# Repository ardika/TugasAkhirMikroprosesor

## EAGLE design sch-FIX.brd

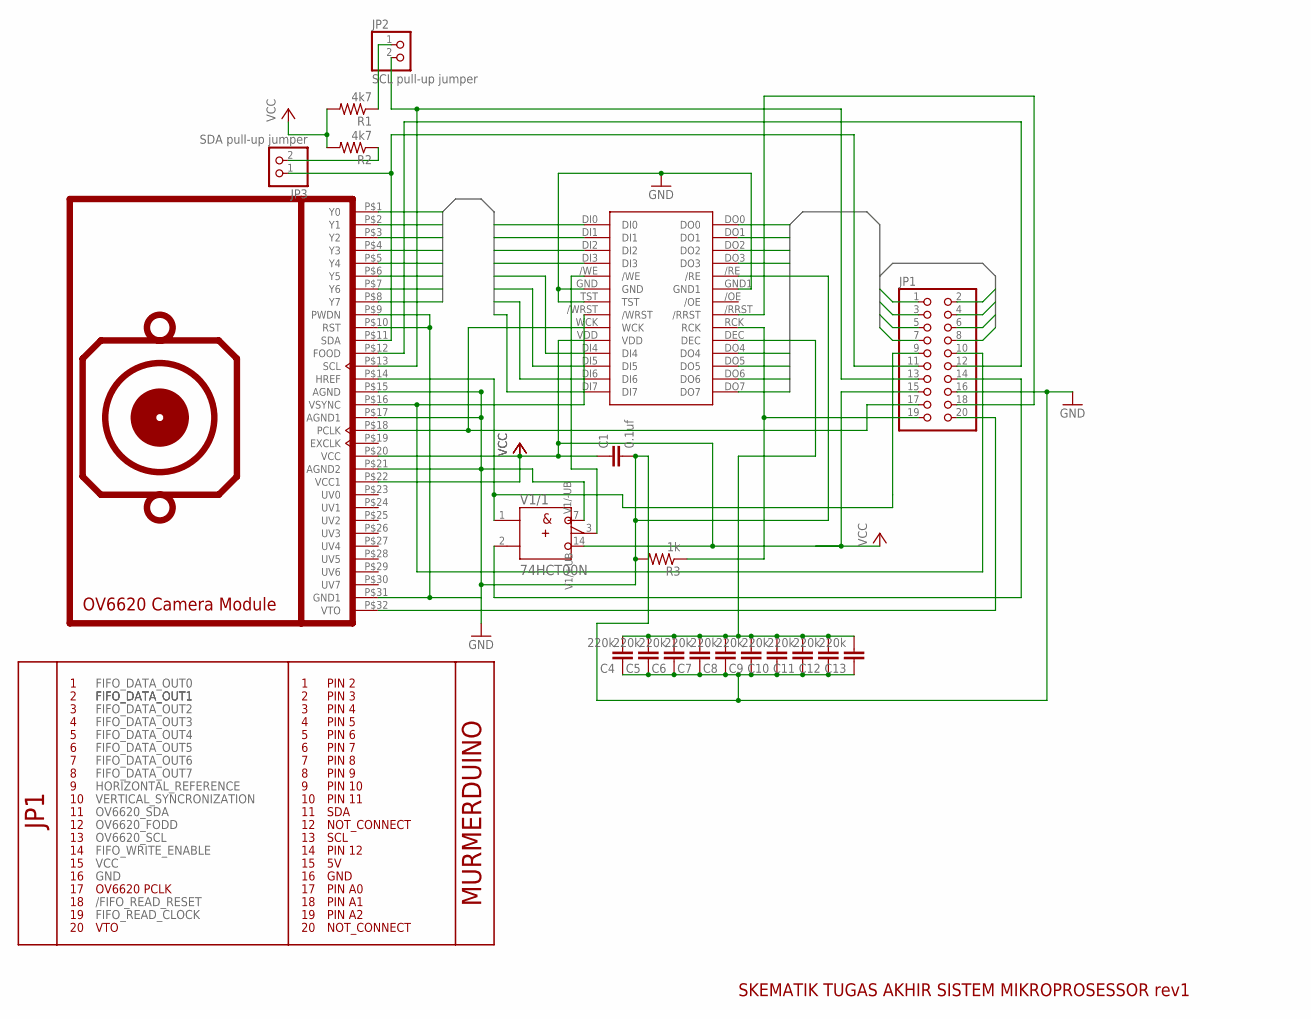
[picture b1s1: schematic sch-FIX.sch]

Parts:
C1: 0.1uf; C025-025X050
C4, C5, C6, C7, C8, C9, C10, C11, C12, C13: 220k; C050-025X075
JP1: PINHD-2X10; 2X10
JP2: SCL pull-up jumper; 1X02
JP3: SDA pull-up jumper; 1X02
R1, R2: 4k7; 0204/7
R3: 1k; 0204/7
U$1: AL422REMOVABLE_MOUNT
U$2: C3088MODULE
V1: 74HCT00N; DIL14

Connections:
/FIFO_READ_RESET: JP1.18, U$1./RRST
DATA0: U$1.DI0, U$2.P$1 (Y0)
DATA1: U$1.DI1, U$2.P$2 (Y1)
DATA2: U$1.DI2, U$2.P$3 (Y2)
DATA3: U$1.DI3, U$2.P$4 (Y3)
DATA4: U$1.DI4, U$2.P$5 (Y4)
DATA5: U$1.DI5, U$2.P$6 (Y5)
DATA6: U$1.DI6, U$2.P$7 (Y6)
DATA7: U$1.DI7, U$2.P$8 (Y7)
FIFO_DATA_OUT0: JP1.1, U$1.DO0
FIFO_DATA_OUT1: JP1.2, U$1.DO1
FIFO_DATA_OUT2: JP1.3, U$1.DO2
FIFO_DATA_OUT3: JP1.4, U$1.DO3
FIFO_DATA_OUT4: JP1.5, U$1.DO4
FIFO_DATA_OUT5: JP1.6, U$1.DO5
FIFO_DATA_OUT6: JP1.7, U$1.DO6
FIFO_DATA_OUT7: JP1.8, U$1.DO7
FIFO_READ_CLOCK: JP1.19, R3.1, U$1.RCK
FIFO_WRITE_ENABLE: JP1.14, V1.2 (B)
GND: C1.2, C4.1, C5.1, C6.1, C7.1, C8.1, C9.1, C10.1, C11.1, C12.1, C13.1, JP1.16, R3.2, U$1./RE, U$2.P$9 (PWDN), U$2.P$10 (RST), U$2.P$15 (AGND), U$2.P$17 (AGND1), U$2.P$21 (AGND2), U$2.P$31 (GND1), V1.7 (-UB)
HORIZONTAL_REFERENCE: JP1.9, U$2.P$14 (HREF), V1.1 (A)
unnamed: JP1.20, U$2.P$32 (VTO)
unnamed: U$1./WE, V1.3 (Y)
unnamed: JP1.17, U$1.WCK, U$2.P$18 (PCLK)
unnamed: JP2.1, R1.1
unnamed: JP3.2, R2.1
unnamed: C4.2, C5.2, C6.2, C7.2, C8.2, C9.2, C10.2, C11.2, C12.2, C13.2, U$1.DEC
unnamed: R1.2, R2.2
unnamed: U$1.GND, U$1.GND1, U$1.TST
OV6620_FODD: JP1.12, U$2.P$12 (FOOD)
OV6620_SCL: JP1.13, JP2.2, U$2.P$13 (SCL)
OV6620_SDA: JP1.11, JP3.1, U$2.P$11 (SDA)
VCC: C1.1, JP1.15, U$1.VDD, U$2.P$20 (VCC), U$2.P$22 (VCC1), V1.14 (+UB)
VERTICAL_SYNCRONIZATION: JP1.10, U$1./WRST, U$2.P$16 (VSYNC)

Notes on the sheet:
VTO
JP1
MURMERDUINO
NOT_CONNECT
PIN 2
PIN 3
PIN 4
PIN 5
PIN 6
PIN 7
PIN 8
PIN 9
PIN 10
PIN 11
SDA
SCL
PIN 12
GND
PIN A0
PIN A1
PIN A2
SKEMATIK TUGAS AKHIR SISTEM MIKROPROSESSOR rev1
OV6620 PCLK

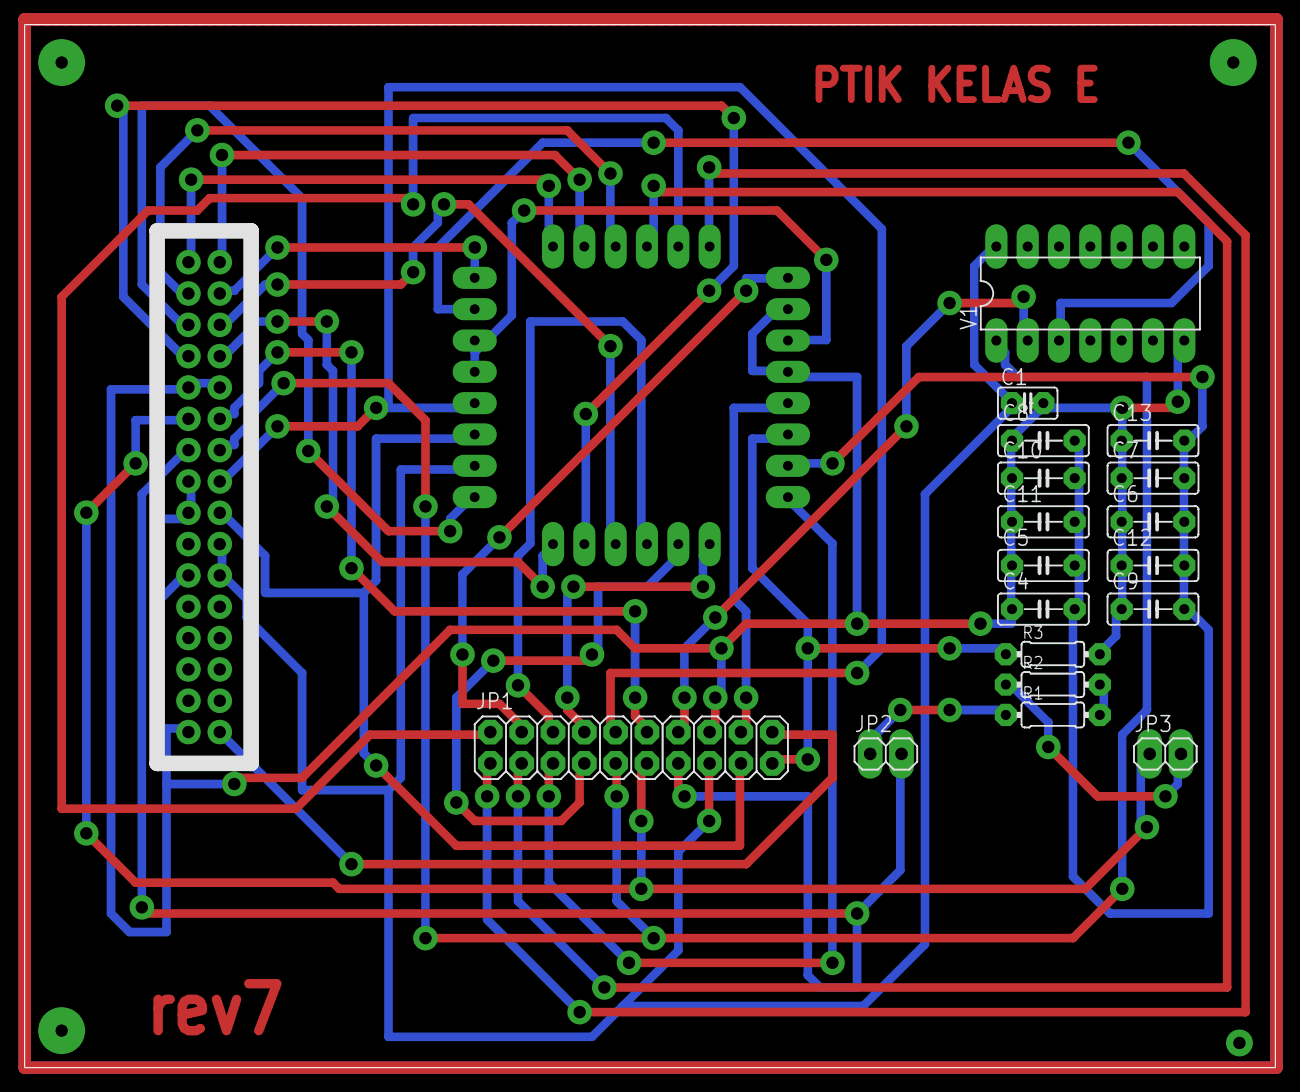
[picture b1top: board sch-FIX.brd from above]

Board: 2 copper layers, 101.4 x 84.6 mm, 20 parts (0 on the bottom side), 34 nets.

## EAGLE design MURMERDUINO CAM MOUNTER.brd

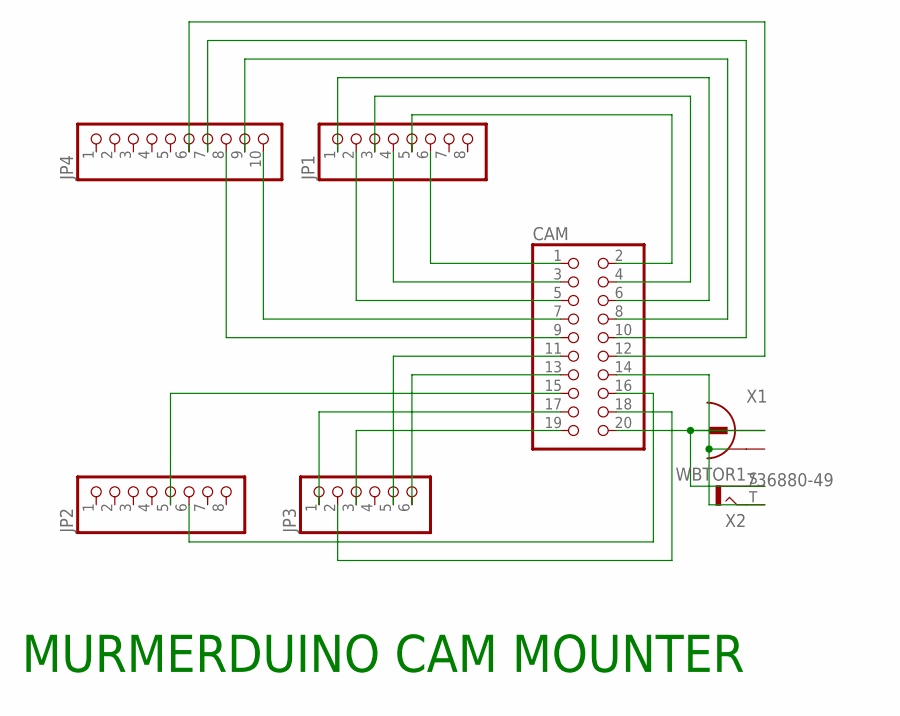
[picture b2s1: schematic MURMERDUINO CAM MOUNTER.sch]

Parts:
CAM: PINHD-2X10; 2X10
JP1, JP2: PINHD-1X8; 1X08
JP3: PINHD-1X6; 1X06
JP4: PINHD-1X10; 1X10
X1: 736880-49
X2: WBTOR1

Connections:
unnamed: CAM.1, JP1.6
unnamed: CAM.2, JP1.5
unnamed: CAM.3, JP1.4
unnamed: CAM.4, JP1.3
unnamed: CAM.5, JP1.2
unnamed: CAM.6, JP1.1
unnamed: CAM.7, JP4.10
unnamed: CAM.8, JP4.9
unnamed: CAM.9, JP4.8
unnamed: CAM.10, JP4.7
unnamed: CAM.11, JP3.5
unnamed: CAM.13, JP3.6
unnamed: CAM.15, JP2.5
unnamed: CAM.16, JP2.6
unnamed: CAM.12, JP4.6
unnamed: CAM.17, JP3.1
unnamed: CAM.18, JP3.2
unnamed: CAM.19, JP3.3
unnamed: CAM.20, X1.1, X2.S
unnamed: CAM.14, X2.T

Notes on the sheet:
MURMERDUINO CAM MOUNTER

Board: 2 copper layers, 7 parts (0 on the bottom side), 20 nets, no tracks yet.

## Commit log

2013-06-17 Release
